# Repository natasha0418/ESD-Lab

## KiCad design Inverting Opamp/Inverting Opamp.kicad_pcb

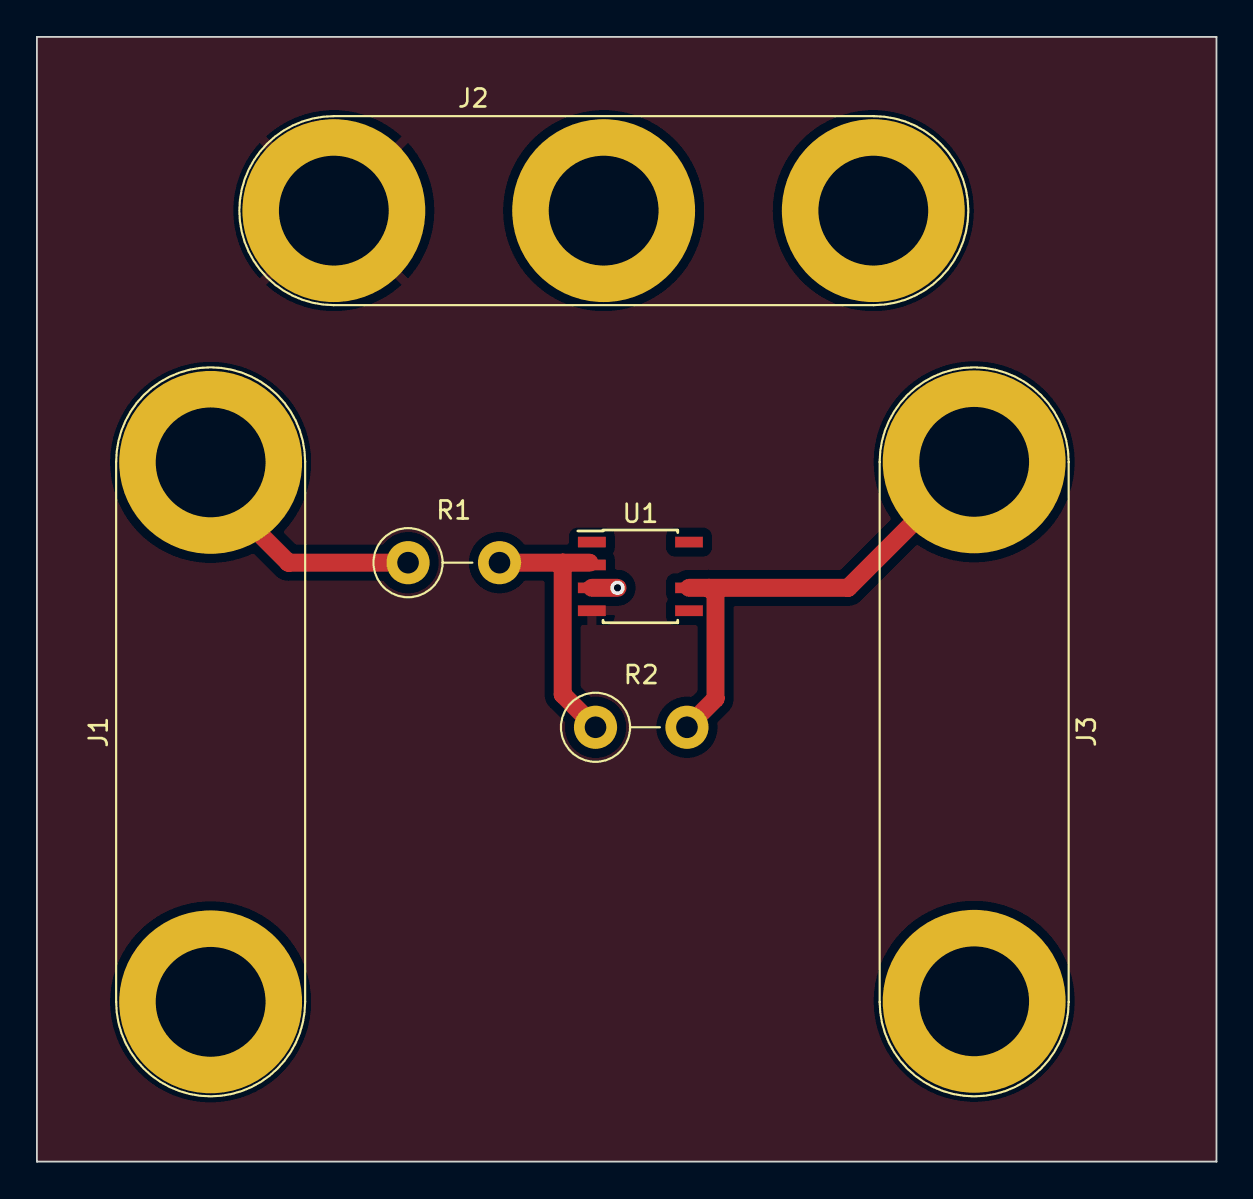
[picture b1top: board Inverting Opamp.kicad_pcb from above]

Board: 2 copper layers, 65.5 x 62.5 mm, 6 parts (0 on the bottom side), 5 nets.

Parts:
J1: Vin; Banana_Jack_2Pin
J2: Conn_01x03; Banana_Jack_3Pin
J3: Vout; Banana_Jack_2Pin
R1: 1k; R_Axial_DIN0411_L9.9mm_D3.6mm_P5.08mm_Vertical
R2: 10k; R_Axial_DIN0411_L9.9mm_D3.6mm_P5.08mm_Vertical
U1: LM741; SOIC-8-N7_3.9x4.9mm_P1.27mm

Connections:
-12V: J2.1, U1.4 (V-)
GND: J1.1, J2.2, J3.2, U1.3 (+)
unnamed: J1.2, R1.1
unnamed: J3.1, R2.2, U1.6
unnamed: R1.2, R2.1, U1.2 (-)
